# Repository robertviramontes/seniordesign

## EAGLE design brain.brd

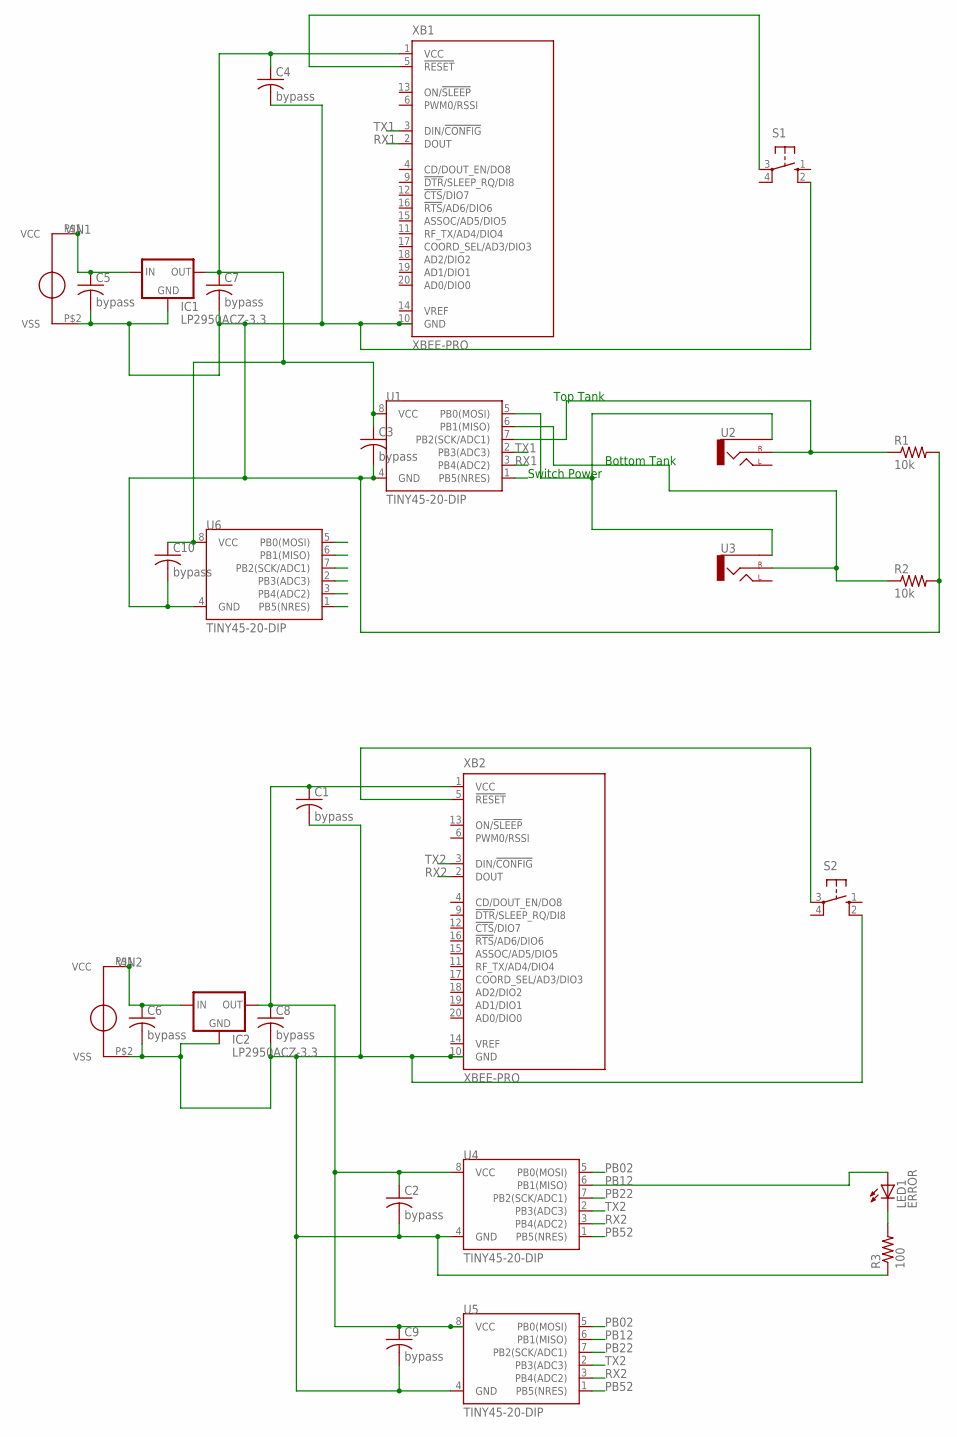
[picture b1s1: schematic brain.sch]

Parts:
C1, C2, C3, C4, C5, C6, C7, C8, C9, C10: bypass; C050-025X075
IC1, IC2: LP2950ACZ-3.3; TO92
LED1: ERROR; LED3MM
R1, R2: 10k; 0207/10; MPN LT3652EMSE#PBF
R3: 100; 0207/10; MPN LT3652EMSE#PBF
S1, S2: 10-XX; B3F-10XX
U1, U4, U5, U6: TINY45-20-DIP; DIP08
U2, U3: AUDIO-JACKPTH; AUDIO-JACK
U$3, U$6: SUNNYBUDDYMOUNT
XB1, XB2: XBEE-PRO

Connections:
GND1: C3.2, C4.2, C5.2, C7.2, C10.2, IC1.2 (GND), R1.2, R2.2, S1.2 (S1), U1.4 (GND), U6.4 (GND), U$3.P$2 (VSS), XB1.10 (GND)
GND2: C1.2, C2.2, C6.2, C8.2, C9.2, IC2.2 (GND), R3.1, S2.2 (S1), U4.4 (GND), U5.4 (GND), U$6.P$2 (VSS), XB2.10 (GND)
unnamed: LED1.K (C), R3.2
unnamed: S2.3, XB2.5 (!RESET)
unnamed: S1.3, XB1.5 (!RESET)
PB01: U1.5 (PB0(MOSI)), U2.SLEEVE, U3.SLEEVE, U6.5 (PB0(MOSI))
PB02: U4.5 (PB0(MOSI)), U5.5 (PB0(MOSI))
PB11: R2.1, U1.6 (PB1(MISO)), U3.RING (RIGHT), U6.6 (PB1(MISO))
PB12: LED1.A, U4.6 (PB1(MISO)), U5.6 (PB1(MISO))
PB21: R1.1, U1.7 (PB2(SCK/ADC1)), U2.RING (RIGHT), U6.7 (PB2(SCK/ADC1))
PB22: U4.7 (PB2(SCK/ADC1)), U5.7 (PB2(SCK/ADC1))
PB51: U1.1 (PB5(NRES)), U6.1 (PB5(NRES))
PB52: U4.1 (PB5(NRES)), U5.1 (PB5(NRES))
RX1: U1.3 (PB4(ADC2)), U6.3 (PB4(ADC2)), XB1.2 (DOUT)
RX2: U4.3 (PB4(ADC2)), U5.3 (PB4(ADC2)), XB2.2 (DOUT)
TX1: U1.2 (PB3(ADC3)), U6.2 (PB3(ADC3)), XB1.3 (DIN/!CONFIG)
TX2: U4.2 (PB3(ADC3)), U5.2 (PB3(ADC3)), XB2.3 (DIN/!CONFIG)
VCC1: C3.1, C4.1, C7.1, C10.1, IC1.1 (OUT), U1.8 (VCC), U6.8 (VCC), XB1.1 (VCC)
VIN1: C5.1, IC1.3 (IN), U$3.P$1 (VCC)
VIN2: C6.1, IC2.3 (IN), U$6.P$1 (VCC)
VOUT2: C1.1, C2.1, C8.1, C9.1, IC2.1 (OUT), U4.8 (VCC), U5.8 (VCC), XB2.1 (VCC)

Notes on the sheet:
Switch Power
Bottom Tank
Top Tank

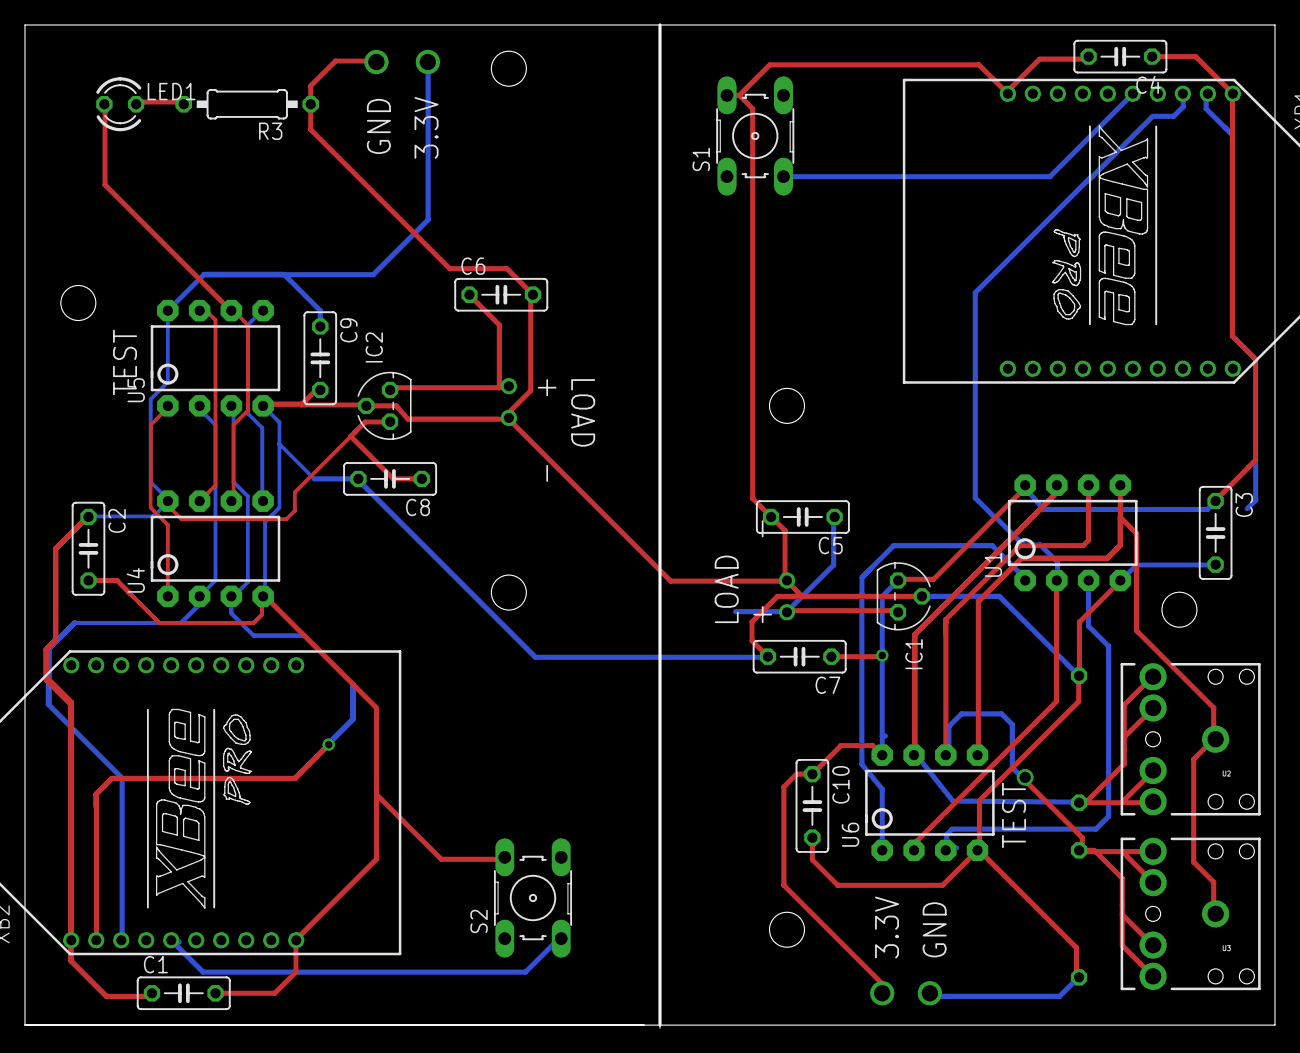
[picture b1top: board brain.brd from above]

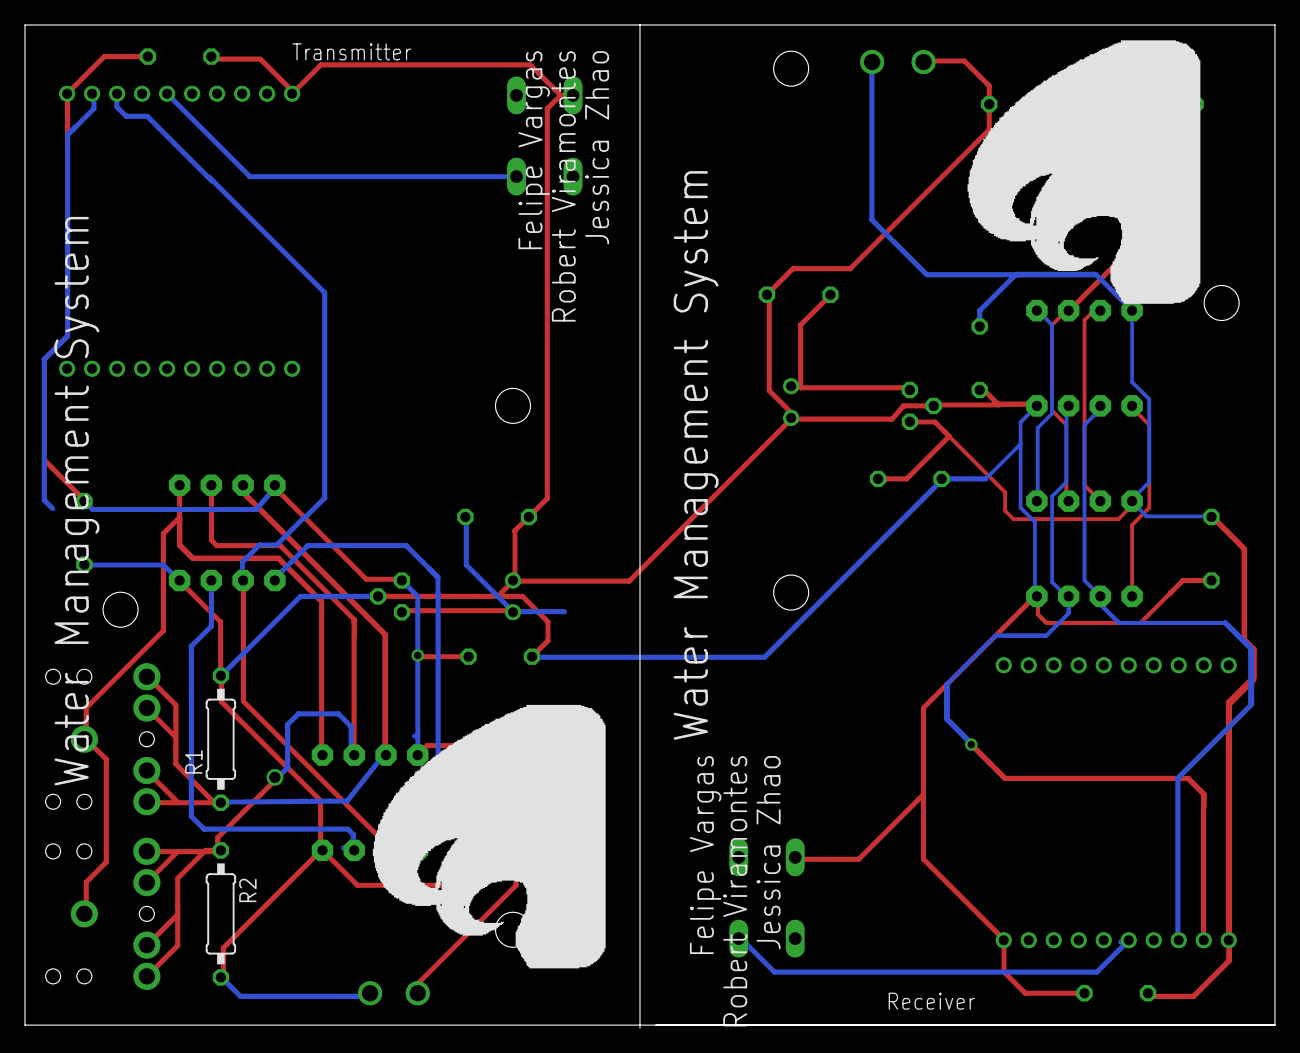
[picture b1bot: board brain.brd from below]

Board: 2 copper layers, 100.0 x 80.3 mm, 28 parts (2 on the bottom side), 21 nets.

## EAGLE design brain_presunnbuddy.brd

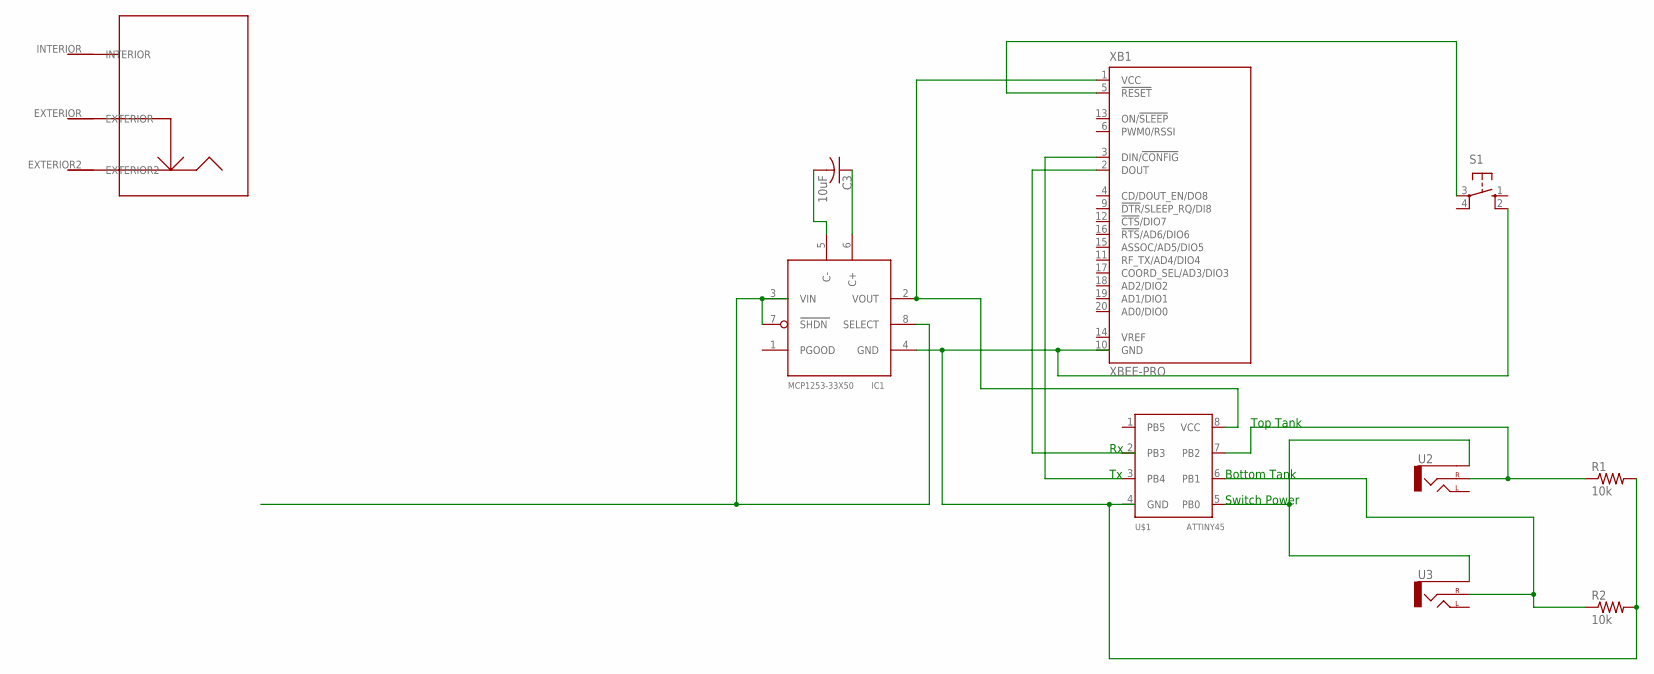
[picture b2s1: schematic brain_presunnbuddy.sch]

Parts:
C3: 10uF; C050-045X075
IC1: MCP1253-33X50; MSOP8; MPN LT3652EMSE#TRPBF
R1, R2: 10k; 0207/10; MPN LT3652EMSE#PBF
S1: 10-XX; B3F-10XX
U2, U3: AUDIO-JACKPTH; AUDIO-JACK
U$1: ATTINY45; SOIC8
U$2: SOLARCELLJACK
XB1: XBEE-PRO

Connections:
BAT: IC1.3 (VIN), IC1.7 (SHDN), IC1.8 (SELECT)
GND: U$1.4 (GND), XB1.10 (GND)
unnamed: IC1.2 (VOUT), U$1.8 (VCC), XB1.1 (VCC)
unnamed: R1.1, U2.RING (RIGHT), U$1.7 (PB2)
unnamed: R2.1, U3.RING (RIGHT), U$1.6 (PB1)
unnamed: U2.SLEEVE, U3.SLEEVE, U$1.5 (PB0)
unnamed: IC1.4 (GND), R1.2, R2.2, S1.2 (S1)
unnamed: C3.1, IC1.6 (C+)
unnamed: U$1.3 (PB4), XB1.3 (DIN/!CONFIG)
unnamed: C3.2, IC1.5 (C-)
unnamed: S1.3, XB1.5 (!RESET)

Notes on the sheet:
Switch Power
Bottom Tank
Top Tank

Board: 2 copper layers, 10 parts (0 on the bottom side), 11 nets, no tracks yet.

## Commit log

2016-04-07 First commit.
2016-04-07 Changed to using the TI LDO for the voltage regulation. Created and added symbol for the Sunny Buddy mounting to allow routing tools to see the electrical connections.
2016-04-07 Added the receiver to schematic and board. Quick layout of the board.
    TODO: Add bypass caps, figure out what the output of the receiver will
    be (LED? something else? should we just make like through holes
    for the ouput of the tiny and the supply and gnd so we can change it
    on the fly?)
2016-04-07 Added some text to board, played a bit with layout/routing.
2016-04-07 wanted to put the gif in the folder...
2016-04-07 Added custom parts library.
2016-04-07 Got rid of library, didn't work as I thought it would.
2016-04-07 Switched the ATTINY45 to the proper package. Added error LED to receiving board. Bypass capacitors added to board. To consider: using vcc/gnd planes for capacitance as well.
2016-04-07 Switched the LDO to the ST device.
2016-04-07 Added test terminals to board. Pre-routing.
2016-04-07 another gif
2016-04-07 uhh we probably moved something. uncertain. nothing major. tied the inputs of the 3.5mm jacks together.
2016-04-08 Added routing. Looks like everything should be good. Put in via line because the $33 boards don't support scoring.
2016-04-08 including zip with the gerber file submited to FreeDFM
2016-04-08 Added bypass capacitors per Sasha's request. Put some identifying information on bottom silkscreen.
2016-04-09 ADDED LOGO TO THE BOARD!!!
2016-04-11 pre-autorouter pt. 2
2016-04-11 Redid a lot of the routing for wire width and such. pre-changing a few back to smaller wires.
2016-04-11 Fixed all wires. Added the drills for stand offs.
2016-05-01 Most recent board changes. also, added the arduino files for the attiny.

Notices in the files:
parts and their libraries:
SparkFun-Connectors: Licensing: CC v3.0 Share-Alike You are welcome to use this library for commercial purposes.
